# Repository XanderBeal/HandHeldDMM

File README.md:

Does this work as a text file???

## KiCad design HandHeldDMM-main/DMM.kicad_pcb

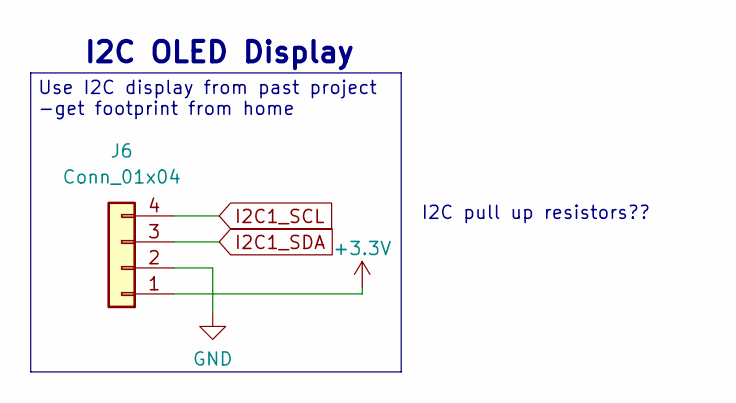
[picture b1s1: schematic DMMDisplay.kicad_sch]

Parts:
J6: Conn_01x04; PinHeader_1x04_P2.54mm_Vertical; LCSC Price 0

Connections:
GND: J6.2; also elsewhere on the board
I2C1_SCL: J6.4; also elsewhere on the board
I2C1_SDA: J6.3; also elsewhere on the board

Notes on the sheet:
Use I2C display from past project -get footprint from home
I2C pull up resistors??
I2C OLED Display

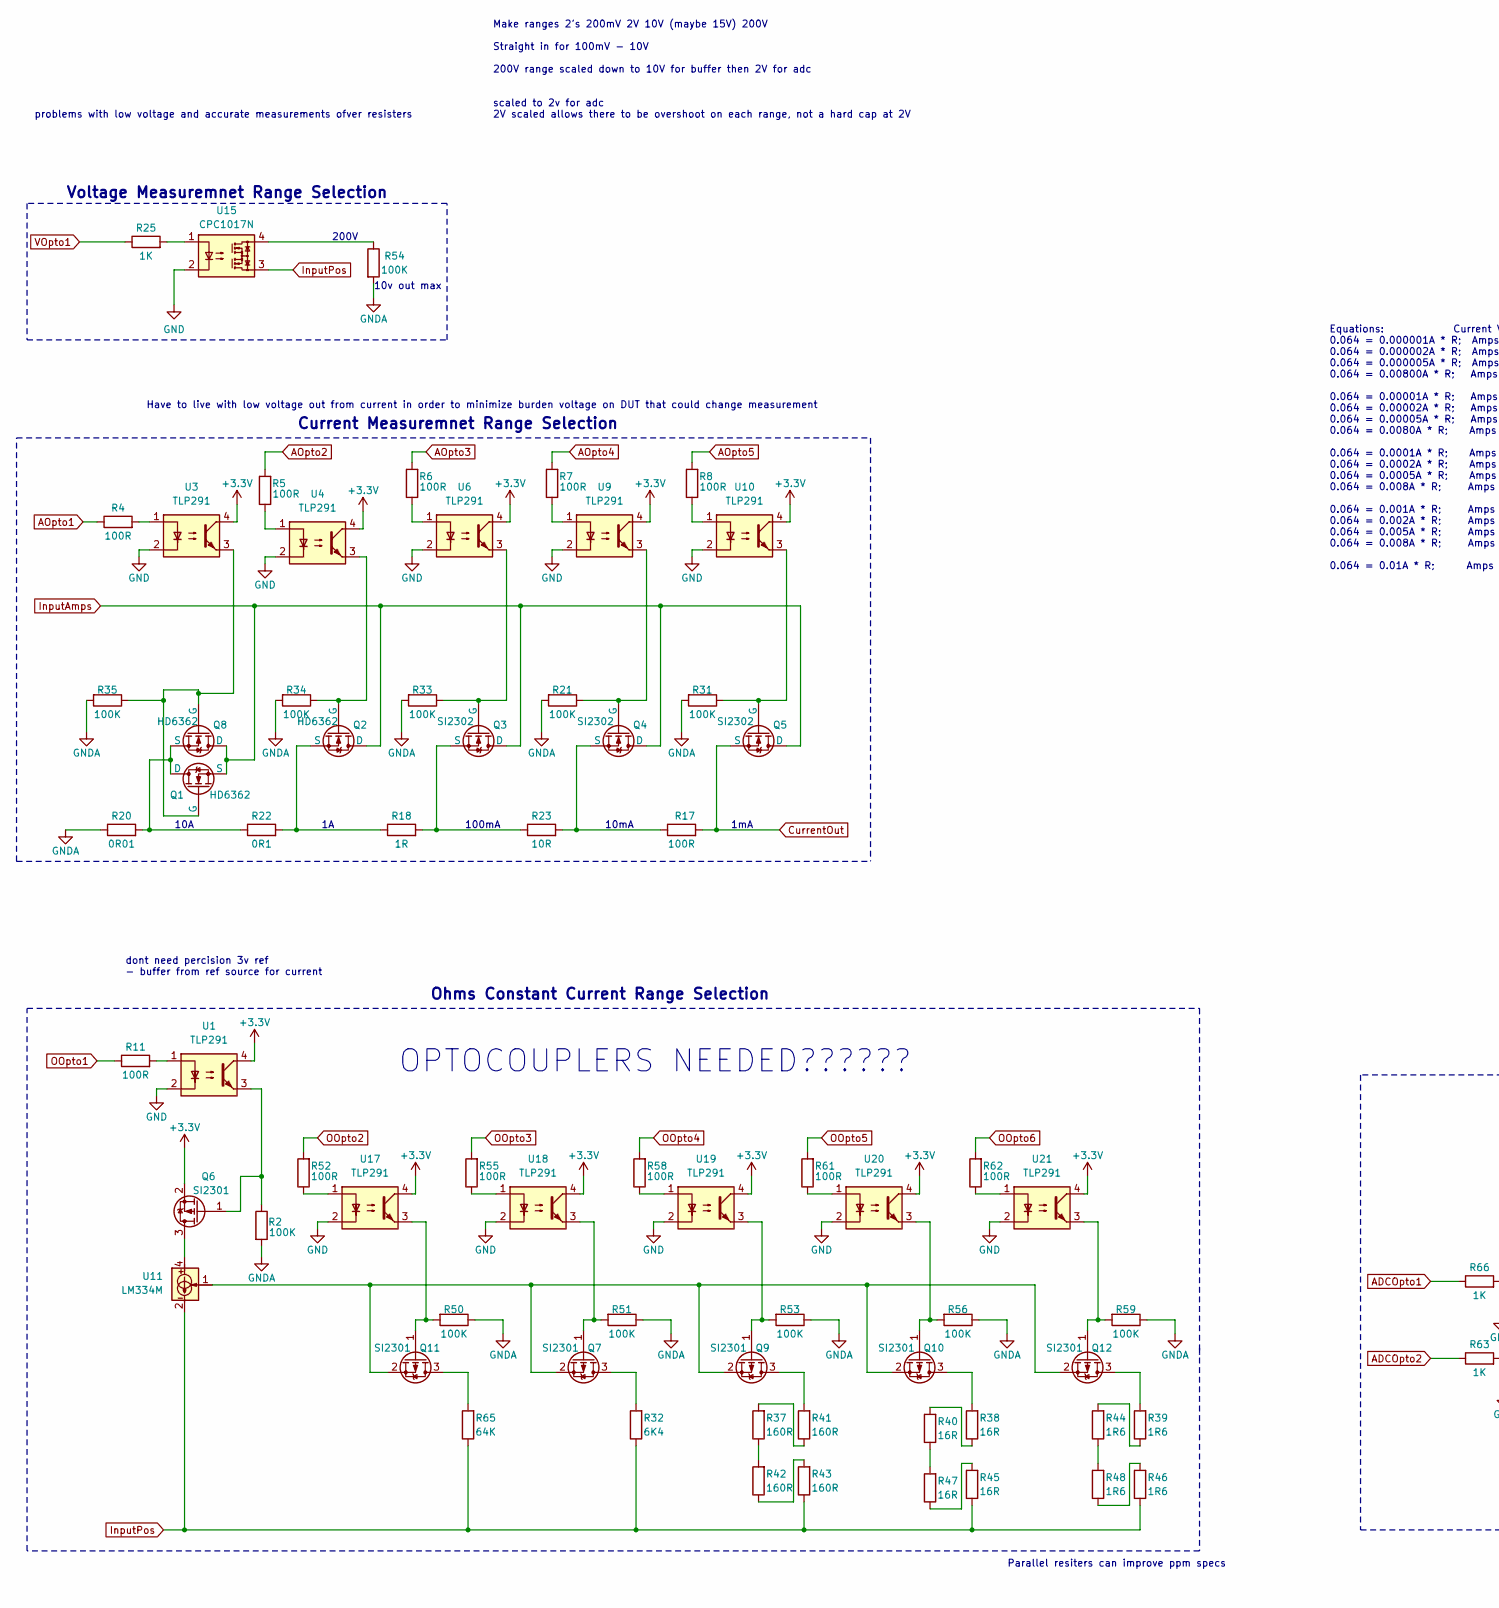
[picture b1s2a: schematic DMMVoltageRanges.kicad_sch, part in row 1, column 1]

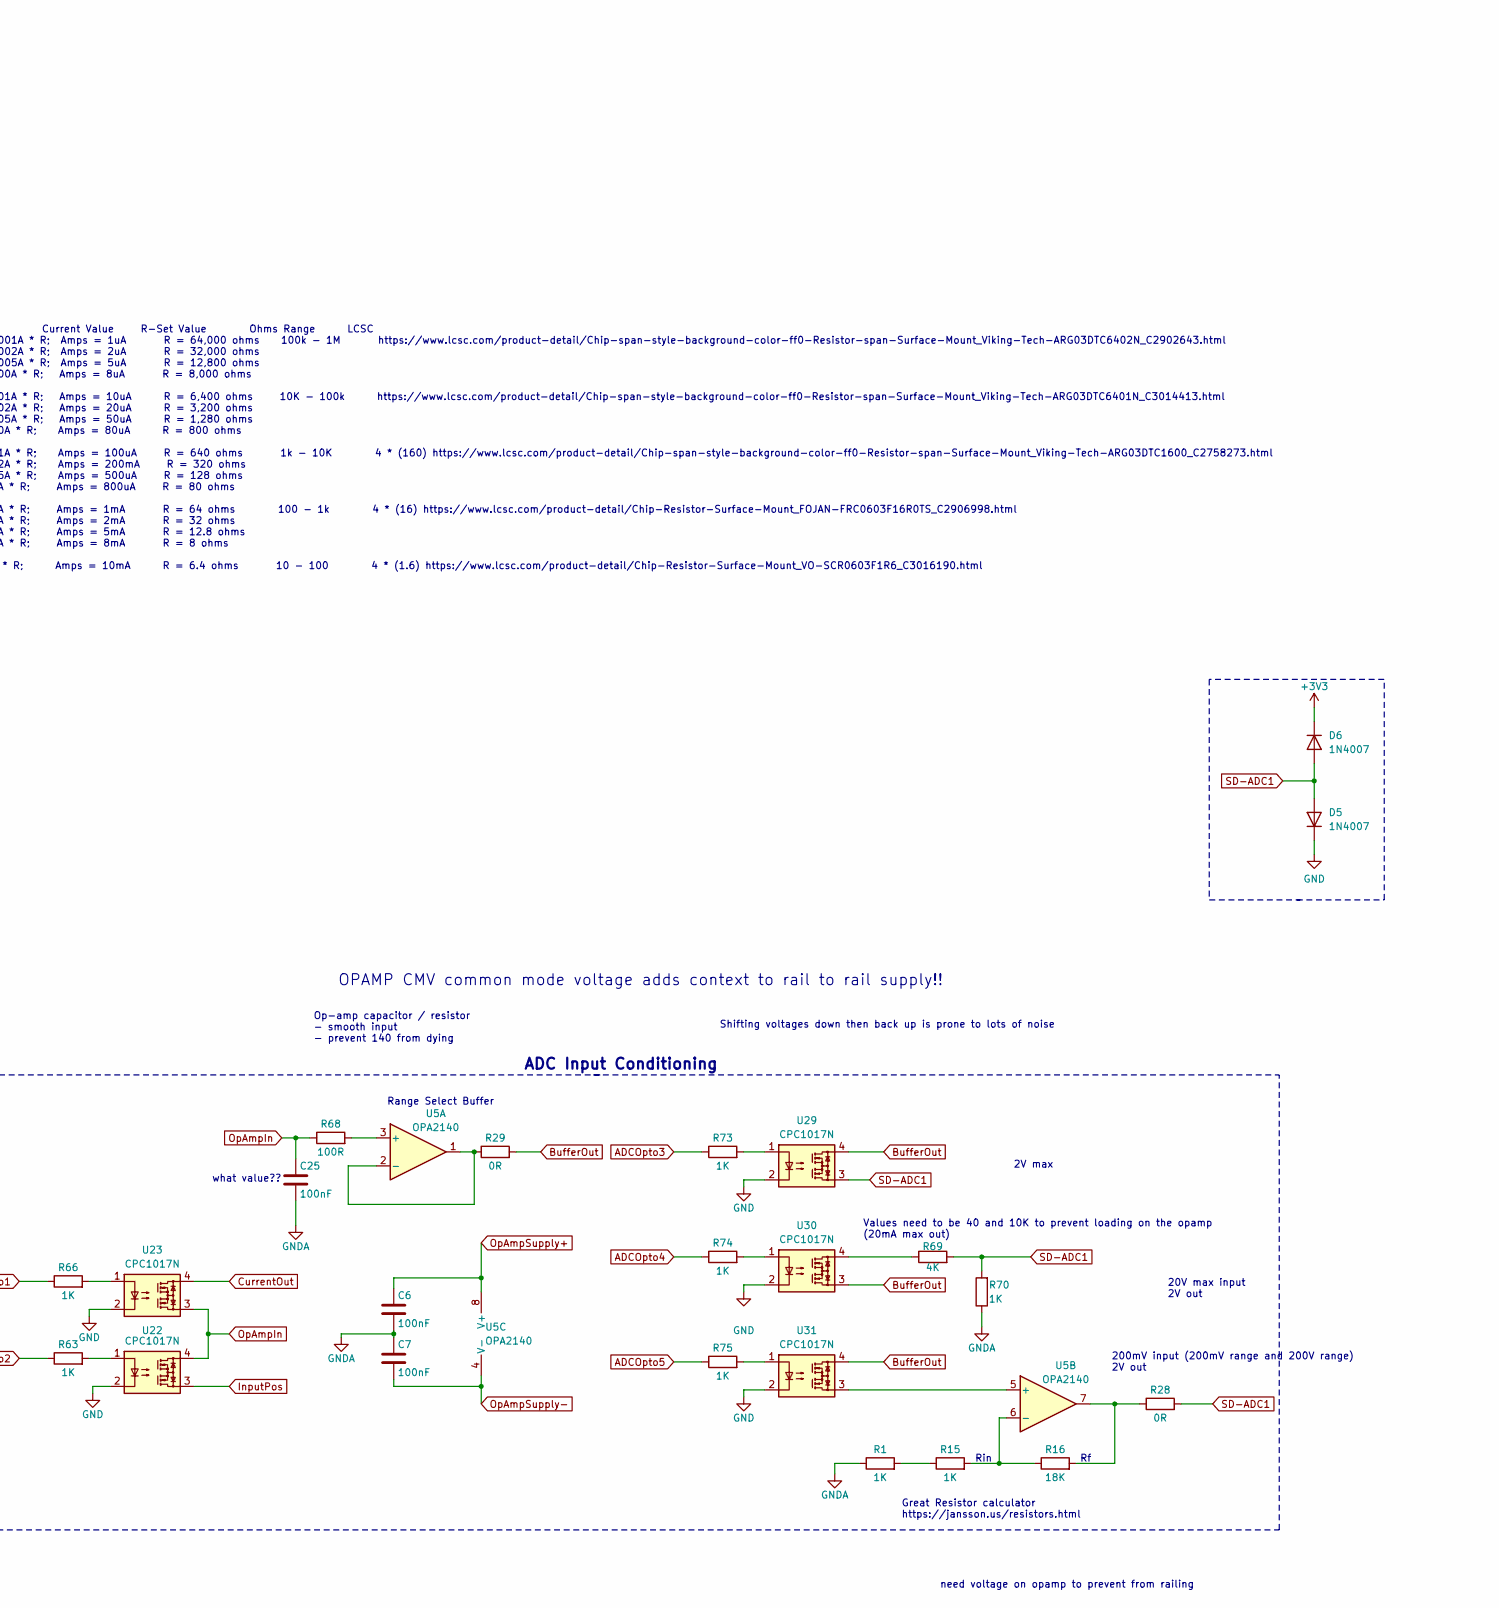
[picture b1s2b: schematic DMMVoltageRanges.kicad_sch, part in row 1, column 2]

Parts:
C6, C7, C25: 100nF; C_0402_1005Metric_Pad0.74x0.62mm_HandSolder; PART# C513772; LCSC Price 0.18
D5, D6: 1N4007; D_DO-41_SOD81_P10.16mm_Horizontal
Q1, Q2, Q8: HD6362; TO-252-2; PART# C5451644; LCSC Price 2
Q3, Q4, Q5: SI2302; SOT-23; PART# C4748714; LCSC Price 0.58
Q6, Q7, Q9, Q10, Q11, Q12: SI2301; SOT-23; PART# C5261052; LCSC Price 0.59
R1, R15, R25, R63, R66, R70, R73, R74, R75: 1K; R_0603_1608Metric_Pad0.98x0.95mm_HandSolder; PART# C5141145; LCSC Price 0.25
R2, R21, R31, R33, R34, R35, R50, R51, R53, R54, R56, R59: 100K; R_0603_1608Metric_Pad0.98x0.95mm_HandSolder; PART# C2906980; LCSC Price 0.09
R4, R5, R6, R7, R8, R11, R52, R55, R58, R61, R62, R68: 100R; R_0402_1005Metric_Pad0.72x0.64mm_HandSolder; PART# C2906860; LCSC Price 0.05
R16: 18K; R_0402_1005Metric_Pad0.72x0.64mm_HandSolder; PART# C2984412; LCSC Price 0.45
R17: 100R; R_2512_6332Metric_Pad1.40x3.35mm_HandSolder; PART# C105063; LCSC Price 0.3
R18: 1R; R_2512_6332Metric_Pad1.40x3.35mm_HandSolder; PART# C5127856; LCSC Price 0.89
R20: 0R01; Shunt L10mm PAD1mm; PART# C487937; LCSC Price 1.62
R22: 0R1; R_2512_6332Metric_Pad1.40x3.35mm_HandSolder; PART# C841792; LCSC Price 0.38
R23: 10R; R_2512_6332Metric_Pad1.40x3.35mm_HandSolder; PART# C105071; LCSC Price 0.48
R28, R29: 0R; R_0603_1608Metric_Pad0.98x0.95mm_HandSolder; PART# C2907080; LCSC Price 0.09
R32: 6K4; R_0402_1005Metric_Pad0.72x0.64mm_HandSolder; PART# C3014413; LCSC Price 0.42
R37, R41, R42, R43: 160R; R_0402_1005Metric_Pad0.72x0.64mm_HandSolder; PART# C2933075; LCSC Price 0.05
R38, R40, R45, R47: 16R; R_0402_1005Metric_Pad0.72x0.64mm_HandSolder; PART# C3015729; LCSC Price 0.05
R39, R44, R46, R48: 1R6; R_0402_1005Metric_Pad0.72x0.64mm_HandSolder; PART# C3015705; LCSC Price 0.07
R65: 64K; R_1206_3216Metric_Pad1.30x1.75mm_HandSolder; PART# C3037190; LCSC Price 0.19
R69: 4K; R_0603_1608Metric_Pad0.98x0.95mm_HandSolder; PART# C2984443; LCSC Price 0.42
U1, U3, U4, U6, U9, U10, U17, U18, U19, U20, U21: TLP291; SOP-4_4.4x2.6mm_P1.27mm; PART# C3018819; LCSC Price 1.32
U5: OPA2140; SOP-8_3.9x4.9mm_P1.27mm; PART# C335586; LCSC Price 15.31
U11: LM334M; SOIC-8_3.9x4.9mm_P1.27mm; PART# C7945; LCSC Price 2.63
U15, U22, U23, U29, U30, U31: CPC1017N; SOP-4_3.8x4.1mm_P2.54mm; PART# C81521; LCSC Price 0.67

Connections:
ADCOpto1: R66.1; also elsewhere on the board
ADCOpto2: R63.1; also elsewhere on the board
ADCOpto3: R73.1; also elsewhere on the board
ADCOpto4: R74.1; also elsewhere on the board
ADCOpto5: R75.1; also elsewhere on the board
AOpto1: R4.1; also elsewhere on the board
AOpto2: R5.2; also elsewhere on the board
AOpto3: R6.2; also elsewhere on the board
AOpto4: R7.2; also elsewhere on the board
AOpto5: R8.2; also elsewhere on the board
BufferOut: R29.2, U29.4, U30.3, U31.4
CurrentOut: Q5.3 (S), R17.2, U23.4
GND: C6.2, C7.1, C25.2, D5.1 (K), R1.1, R2.2, R20.1, R21.2, R31.2, R33.2, R34.2, R35.2, R50.1, R51.1, R53.1, R54.2, R56.1, R59.1, R70.1, U1.2, U3.2, U4.2, U6.2, U9.2, U10.2, U15.2, U17.2, U18.2, U19.2, U20.2, U21.2, U22.2, U23.2, U29.2, U30.2, U31.2; also elsewhere on the board
InputAmps: Q1.3 (S), Q2.2 (D), Q3.2 (D), Q4.2 (D), Q5.2 (D), Q8.2 (D); also elsewhere on the board
InputPos: R32.1, R43.1, R45.1, R46.1, R65.1, U11.2, U11.3, U11.6, U11.7, U15.3, U22.3; also elsewhere on the board
unnamed: Q1.2 (D), Q8.3 (S), R20.2, R22.1
unnamed: Q1.1 (G), Q8.1 (G), R35.1, U3.3
unnamed: Q2.1 (G), R34.1, U4.3
unnamed: Q2.3 (S), R18.1, R22.2
unnamed: Q3.1 (G), R33.1, U6.3
unnamed: Q3.3 (S), R18.2, R23.1
unnamed: Q4.1 (G), R21.1, U9.3
unnamed: Q4.3 (S), R17.1, R23.2
unnamed: Q5.1 (G), R31.1, U10.3
unnamed: Q6.3 (D), U11.4
unnamed: Q6.1 (G), R2.1, U1.3
unnamed: Q7.3 (D), R32.2
unnamed: Q7.1 (G), R51.2, U18.3
unnamed: Q9.3 (D), R41.2
unnamed: Q9.1 (G), R53.2, U19.3
unnamed: Q10.3 (D), R38.2
unnamed: Q10.1 (G), R56.2, U20.3
unnamed: Q7.2 (S), Q9.2 (S), Q10.2 (S), Q11.2 (S), Q12.2 (S), U11.1
unnamed: Q11.3 (D), R65.2
unnamed: Q11.1 (G), R50.2, U17.3
unnamed: Q12.3 (D), R39.2
unnamed: Q12.1 (G), R59.2, U21.3
unnamed: R1.2, R15.1
unnamed: R4.2, U3.1
unnamed: R5.1, U4.1
unnamed: R6.1, U6.1
unnamed: R7.1, U9.1
unnamed: R8.1, U10.1
unnamed: R11.2, U1.1
unnamed: R16.2, R28.1, U5.7
unnamed: R25.2, U15.1
unnamed: R37.1, R42.2
unnamed: R37.2, R41.1
unnamed: R38.1, R40.2
unnamed: R39.1, R44.2
unnamed: R40.1, R47.2
unnamed: R42.1, R43.2
unnamed: R44.1, R48.2
unnamed: R45.2, R47.1
unnamed: R46.2, R48.1
unnamed: R52.1, U17.1
unnamed: R54.1, U15.4
unnamed: R55.1, U18.1
unnamed: R58.1, U19.1
unnamed: R61.1, U20.1
unnamed: R62.1, U21.1
unnamed: R63.2, U22.1
unnamed: R66.2, U23.1
unnamed: R69.1, U30.4
unnamed: R73.2, U29.1
unnamed: R74.2, U30.1
unnamed: R75.2, U31.1
unnamed: R68.2, U5.3 (+)
unnamed: R29.1, U5.1, U5.2 (-)
unnamed: U5.5 (+), U31.3
unnamed: R15.2, R16.1, U5.6 (-)
OOpto1: R11.1; also elsewhere on the board
OOpto2: R52.2; also elsewhere on the board
OOpto3: R55.2; also elsewhere on the board
OOpto4: R58.2; also elsewhere on the board
OOpto5: R61.2; also elsewhere on the board
OOpto6: R62.2; also elsewhere on the board
OpAmpIn: C25.1, R68.1, U22.4, U23.3
OpAmpSupply+: C6.1, U5.8 (V+); also elsewhere on the board
OpAmpSupply-: C7.2, U5.4 (V-); also elsewhere on the board
SD-ADC1: D5.2 (A), D6.2 (A), R28.2, R69.2, R70.2, U29.3; also elsewhere on the board
VOpto1: R25.1; also elsewhere on the board

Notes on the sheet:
Range Select Buffer
Voltage Measuremnet Range Selection
2V max
need voltage on opamp to prevent from railing
10v out max
Op-amp capacitor / resistor - smooth input - prevent 140 from dying
10mA
Values need to be 40 and 10K to prevent loading on the opamp (20mA max out)
1mA
Have to live with low voltage out from current in order to minimize burden voltage on DUT that could change measurement
Current Measuremnet Range Selection
Great Resistor calculator https://jansson.us/resistors.html
Shifting voltages down then back up is prone to lots of noise
Parallel resiters can improve ppm specs
dont need percision 3v ref - buffer from ref source for current
ADC Input Conditioning
Ohms Constant Current Range Selection
Rin
OPTOCOUPLERS NEEDED??????
Equations: Current Value R-Set Value Ohms Range LCSC 0.064 = 0.000001A * R; Amps = 1uA R = 64,000 ohms 100k - 1M https://www.lcsc.com/product-detail/Chip-span-style-background-color-ff0-Resistor-span-Surface-Mount_Viking-Tech-ARG03DTC6402N_C2902643.html 0.064 = 0.000002A * R; Amps = 2uA R = 32,000 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
10A
200mV input (200mV range and 200V range) 2V out
Make ranges 2's 200mV 2V 10V (maybe 15V) 200V Straight in for 100mV - 10V 200V range scaled down to 10V for buffer then 2V for adc scaled to 2v for adc 2V scaled allows there to be overshoot on each range, not a hard cap at 2V
OPAMP CMV common mode voltage adds context to rail to rail supply!!
200V
100mA
what value??
20V max input 2V out
problems with low voltage and accurate measurements ofver resisters

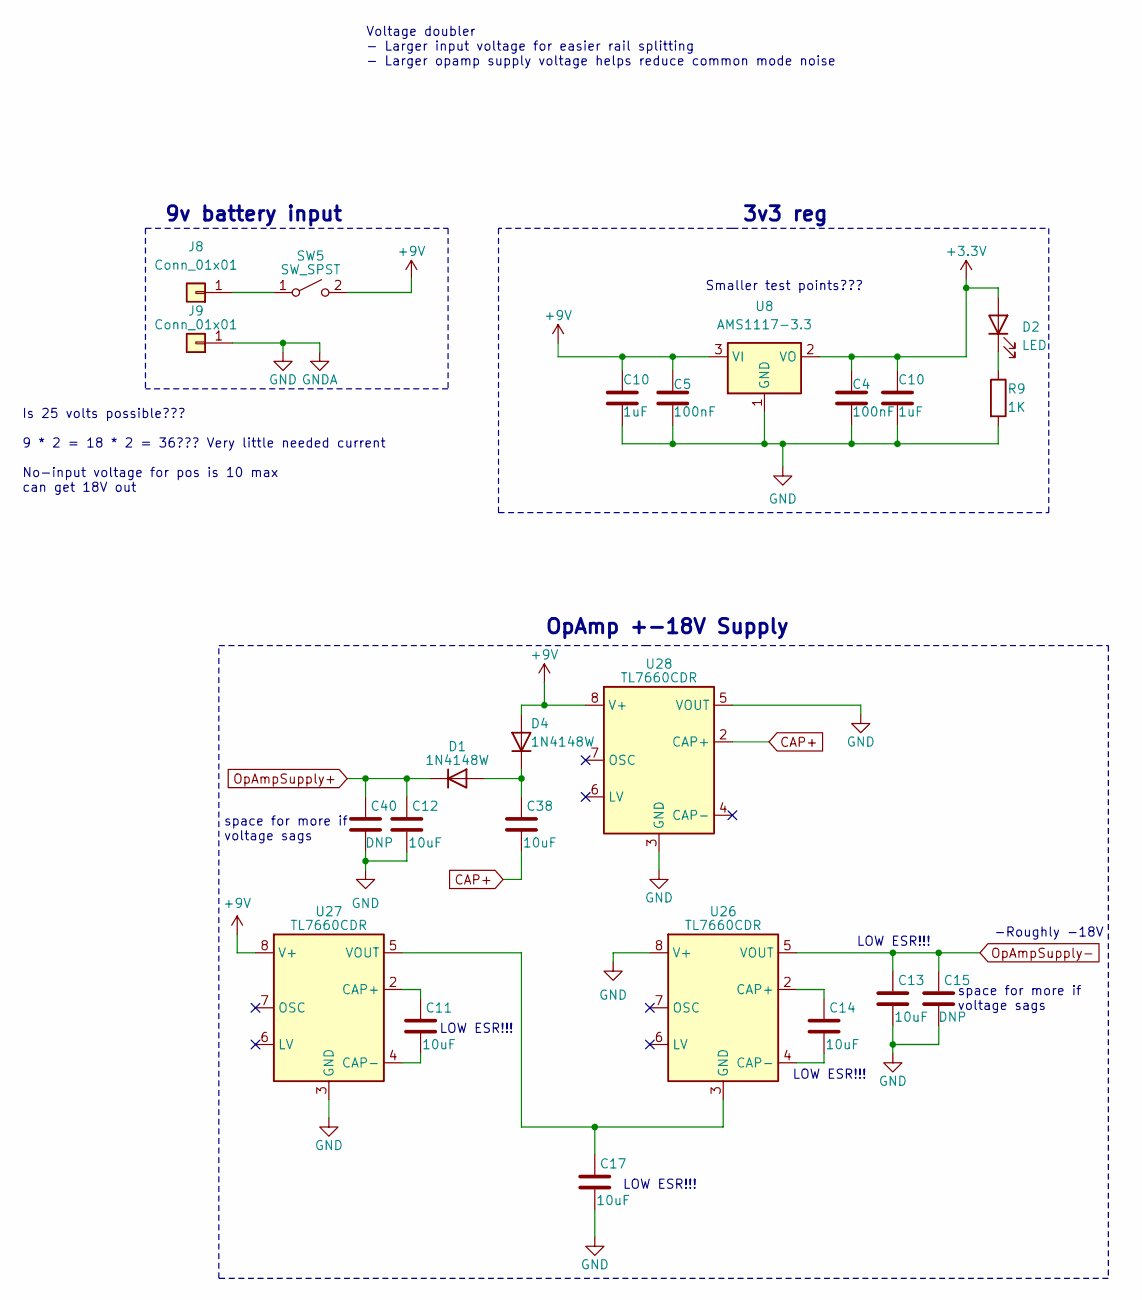
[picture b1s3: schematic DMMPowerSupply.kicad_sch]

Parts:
C4, C5: 100nF; C_0402_1005Metric_Pad0.74x0.62mm_HandSolder; PART# C513772; LCSC Price 0.18
C10: 1uF; C_0402_1005Metric_Pad0.74x0.62mm_HandSolder; PART# C14445; LCSC Price 0.17
C11, C12, C13, C14, C17, C38: 10uF; C_1206_3216Metric_Pad1.33x1.80mm_HandSolder; PART# C5189826; LCSC Price 0.41
C15, C40: DNP; C_1206_3216Metric_Pad1.33x1.80mm_HandSolder
D1, D4: 1N4148W; D_SOD-123; PART# C917030; LCSC Price 0.52
D2: LED; LED_0603_1608Metric_Pad1.05x0.95mm_HandSolder; LCSC Price 0
J8, J9: Conn_01x01; TestPoint_THTPad_3.0x3.0mm_Drill1.5mm; LCSC Price 0
R9: 1K; R_0603_1608Metric_Pad0.98x0.95mm_HandSolder; PART# C5141145; LCSC Price 0.25
SW5: SW_SPST; Dip Switch
U8: AMS1117-3.3; SOT-89-3; PART# C5345982; LCSC Price 0.39
U26, U27, U28: TL7660CDR; SOIC-8_3.9x4.9mm_P1.27mm; PART# C130206

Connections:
CAP+: C38.1, U28.2 (CAP+)
GND: C4.2, C5.2, C10.2, C12.1, C13.1, C15.1, C17.1, C40.1, J9.1, R9.2, U8.1 (GND), U26.8 (V+), U27.3 (GND), U28.3 (GND), U28.5 (VOUT); also elsewhere on the board
unnamed: C38.2, D1.2 (A), D4.1 (K)
unnamed: D2.1 (K), R9.1
unnamed: J8.1, SW5.1 (A)
unnamed: C14.2, U26.2 (CAP+)
unnamed: C14.1, U26.4 (CAP-)
unnamed: C17.2, U26.3 (GND), U27.5 (VOUT)
unnamed: C11.2, U27.2 (CAP+)
unnamed: C11.1, U27.4 (CAP-)
OpAmpSupply+: C12.2, C40.2, D1.1 (K); also elsewhere on the board
OpAmpSupply-: C13.2, C15.2, U26.5 (VOUT); also elsewhere on the board

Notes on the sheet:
-Roughly -18V
LOW ESR!!!
3v3 reg
Is 25 volts possible??? 9 * 2 = 18 * 2 = 36??? Very little needed current No-input voltage for pos is 10 max can get 18V out
OpAmp +-18V Supply
Smaller test points???
Voltage doubler - Larger input voltage for easier rail splitting - Larger opamp supply voltage helps reduce common mode noise
9v battery input
space for more if voltage sags

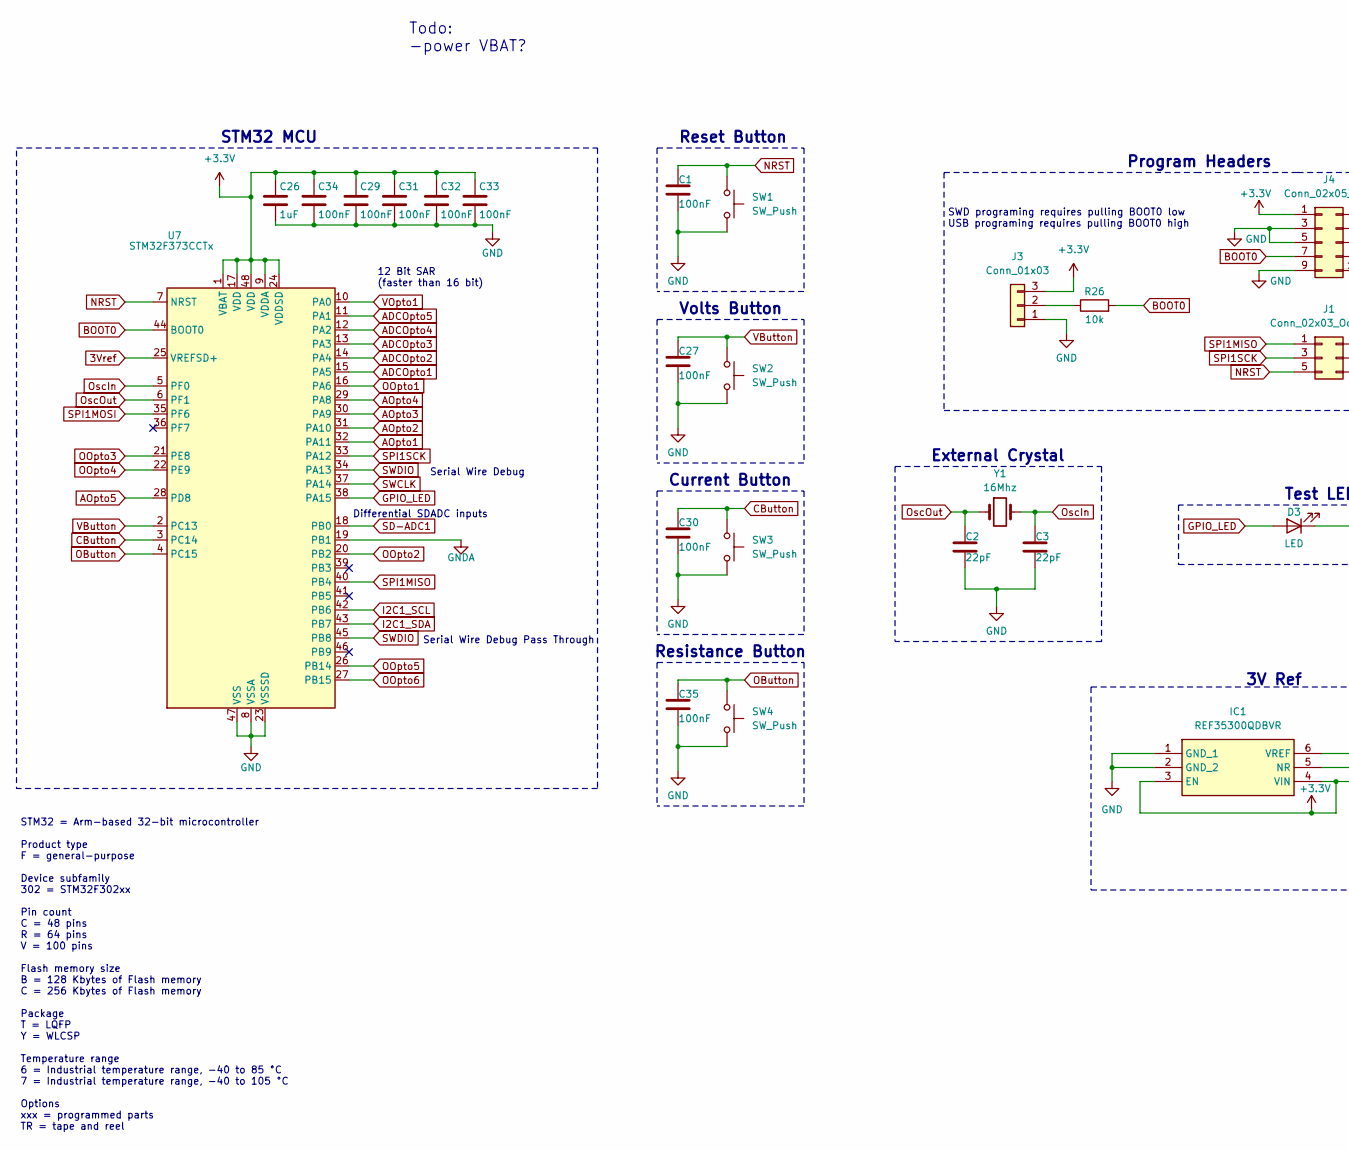
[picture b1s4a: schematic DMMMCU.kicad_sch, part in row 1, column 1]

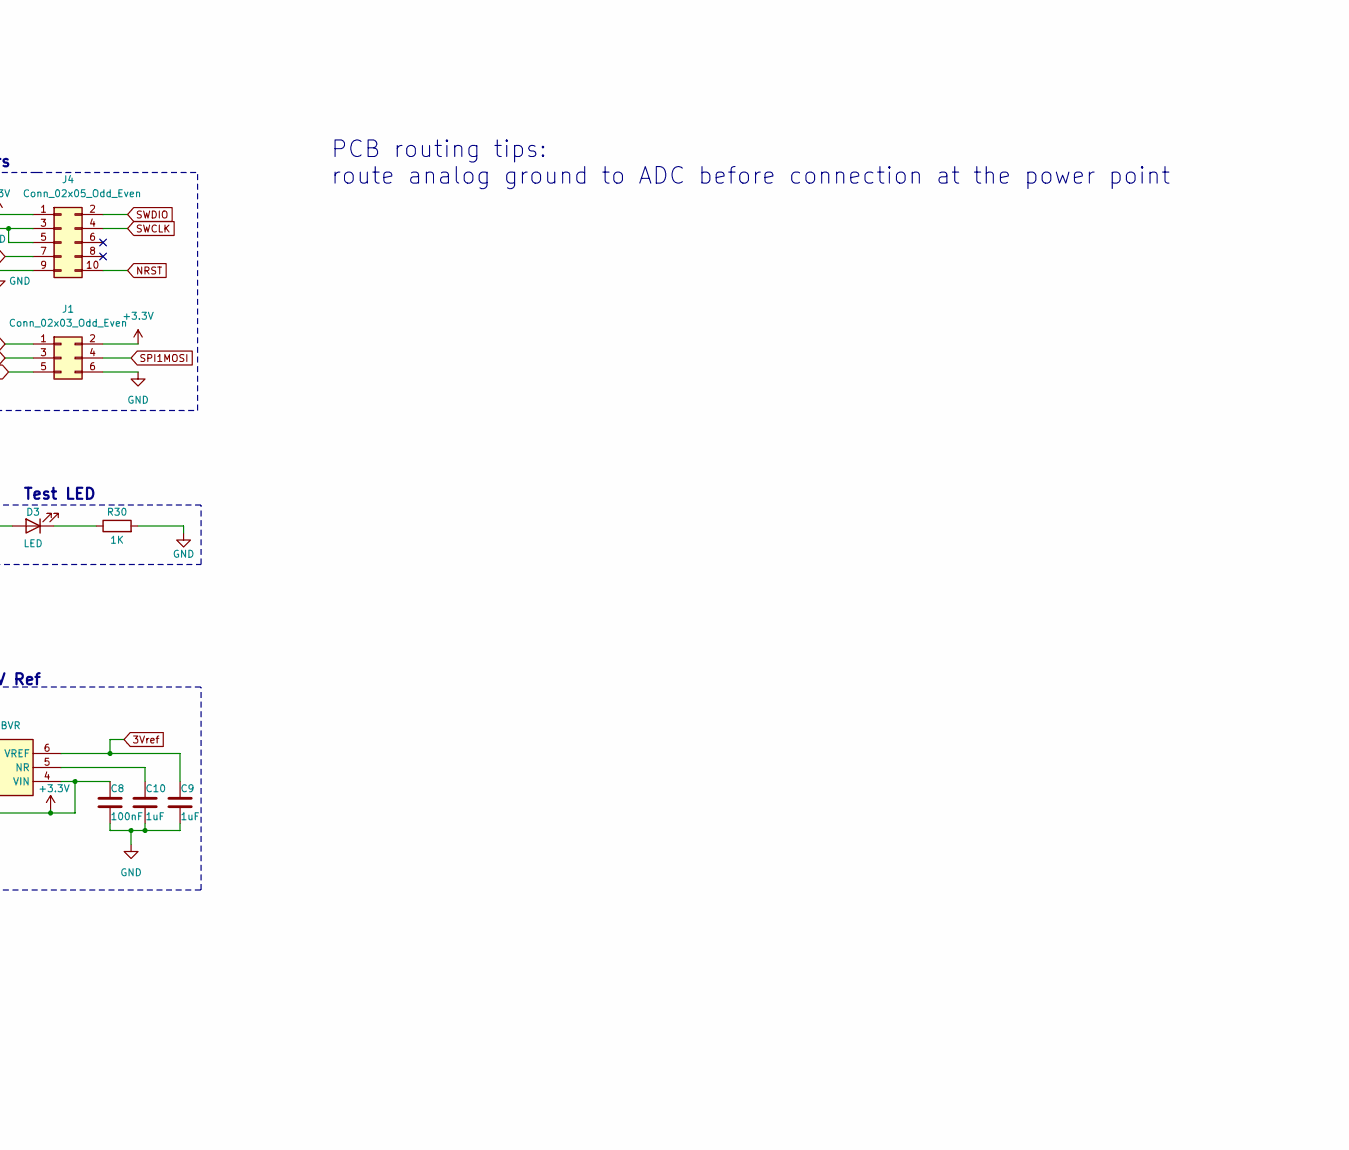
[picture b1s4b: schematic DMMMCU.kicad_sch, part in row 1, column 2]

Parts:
C1, C8, C27, C29, C30, C31, C32, C33, C34, C35: 100nF; C_0402_1005Metric_Pad0.74x0.62mm_HandSolder; PART# C513772; LCSC Price 0.18
C2, C3: 22pF; C_0402_1005Metric_Pad0.74x0.62mm_HandSolder; LCSC Price 0
C9, C10, C26: 1uF; C_0402_1005Metric_Pad0.74x0.62mm_HandSolder; PART# C14445; LCSC Price 0.17
D3: LED; LED_0603_1608Metric_Pad1.05x0.95mm_HandSolder; LCSC Price 0
IC1: REF35300QDBVR; SOT-23-6; PART# C6643299; LCSC Price 3.09
J1: Conn_02x03_Odd_Even; PinHeader_2x03_P2.54mm_Vertical; LCSC Price 0
J3: Conn_01x03; PinHeader_1x03_P2.54mm_Vertical; LCSC Price 0
J4: Conn_02x05_Odd_Even; PinHeader_2x05_P2.54mm_Vertical; LCSC Price 0
R26: 10k; R_0603_1608Metric_Pad0.98x0.95mm_HandSolder; PART# C103199; LCSC Price copy
R30: 1K; R_0603_1608Metric_Pad0.98x0.95mm_HandSolder; PART# C5141145; LCSC Price 0.25
SW1, SW2, SW3, SW4: SW_Push; SW_SPST_B3S-1000; PART# C2888900; LCSC Price 0.4
U7: STM32F373CCTx; LQFP-48_7x7mm_P0.5mm; PART# C89403; LCSC Price 20.27
Y1: 16Mhz; Crystal_DS10_D1.0mm_L4.3mm_Vertical; LCSC Price 0

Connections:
3Vref: C9.1, IC1.6 (VREF), U7.25 (VREFSD+)
ADCOpto1: U7.15 (PA5); also elsewhere on the board
ADCOpto2: U7.14 (PA4); also elsewhere on the board
ADCOpto3: U7.13 (PA3); also elsewhere on the board
ADCOpto4: U7.12 (PA2); also elsewhere on the board
ADCOpto5: U7.11 (PA1); also elsewhere on the board
AOpto1: U7.32 (PA11); also elsewhere on the board
AOpto2: U7.31 (PA10); also elsewhere on the board
AOpto3: U7.30 (PA9); also elsewhere on the board
AOpto4: U7.29 (PA8); also elsewhere on the board
AOpto5: U7.28 (PD8); also elsewhere on the board
BOOT0: J4.7, R26.2, U7.44 (BOOT0)
CButton: C30.1, SW3.1, U7.3 (PC14)
GND: C1.2, C2.2, C3.2, C8.2, C9.2, C10.2, C26.2, C27.2, C29.2, C30.2, C31.2, C32.2, C33.2, C34.2, C35.2, IC1.1 (GND_1), IC1.2 (GND_2), J1.6, J3.1, J4.3, J4.5, J4.9, R30.2, SW1.2, SW2.2, SW3.2, SW4.2, U7.8 (VSSA), U7.19 (PB1), U7.23 (VSSSD), U7.47 (VSS); also elsewhere on the board
GPIO_LED: D3.2 (A), U7.38 (PA15)
I2C1_SCL: U7.42 (PB6); also elsewhere on the board
I2C1_SDA: U7.43 (PB7); also elsewhere on the board
NRST: C1.1, J1.5, J4.10, SW1.1, U7.7 (NRST)
unnamed: D3.1 (K), R30.1
unnamed: J3.2, R26.1
OButton: C35.1, SW4.1, U7.4 (PC15)
OOpto1: U7.16 (PA6); also elsewhere on the board
OOpto2: U7.20 (PB2); also elsewhere on the board
OOpto3: U7.21 (PE8); also elsewhere on the board
OOpto4: U7.22 (PE9); also elsewhere on the board
OOpto5: U7.26 (PB14); also elsewhere on the board
OOpto6: U7.27 (PB15); also elsewhere on the board
OscIn: C3.1, U7.5 (PF0), Y1.2
OscOut: C2.1, U7.6 (PF1), Y1.1
SD-ADC1: U7.18 (PB0); also elsewhere on the board
SPI1MISO: J1.1, U7.40 (PB4)
SPI1MOSI: J1.4, U7.35 (PF6)
SPI1SCK: J1.3, U7.33 (PA12)
SWCLK: J4.4, U7.37 (PA14)
SWDIO: J4.2, U7.34 (PA13), U7.45 (PB8)
VButton: C27.1, SW2.1, U7.2 (PC13)
VOpto1: U7.10 (PA0); also elsewhere on the board

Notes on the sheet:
External Crystal
Volts Button
STM32 MCU
SWD programing requires pulling BOOT0 low USB programing requires pulling BOOT0 high
Resistance Button
3V Ref
Reset Button
Current Button
Test LED
Todo: -power VBAT?
Program Headers
PCB routing tips: route analog ground to ADC before connection at the power point
Serial Wire Debug
Serial Wire Debug Pass Through
Differential SDADC inputs
12 Bit SAR (faster than 16 bit)
STM32 = Arm-based 32-bit microcontroller Product type F = general-purpose Device subfamily 302 = STM32F302xx Pin count C = 48 pins R = 64 pins V = 100 pins Flash memory size B = 128 Kbytes of Flash memory C = 256 Kbytes of Flash memory Package T = LQFP Y = WLCSP Temperature range 6 = Industrial tem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

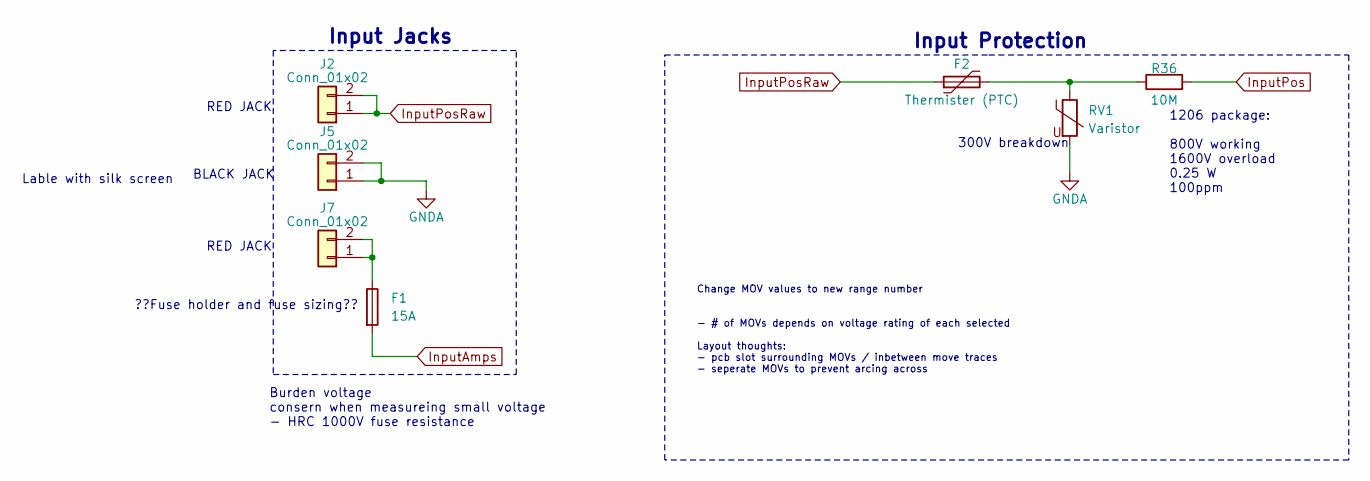
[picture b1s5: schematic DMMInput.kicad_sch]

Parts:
F1: 15A; Fuse holder; PART# C3130; LCSC Price 0.35
F2: Thermister (PTC); R_Axial_DIN0207_L6.3mm_D2.5mm_P7.62mm_Horizontal; LCSC Price 0
J2, J7: Conn_01x02; Bannana Input Jack; PART# C7437321; LCSC Price 0.9180
J5: Conn_01x02; Bannana Input Jack; PART# C7437322; LCSC Price 0.9180
R36: 10M; R_1206_3216Metric_Pad1.30x1.75mm_HandSolder; PART# C2078785; LCSC Price 1.19
RV1: Varistor; R_Axial_DIN0207_L6.3mm_D2.5mm_P5.08mm_Vertical; PART# C283925; LCSC Price 0.6

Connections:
GND: J5.1, J5.2, RV1.2; also elsewhere on the board
InputAmps: F1.2; also elsewhere on the board
InputPos: R36.2; also elsewhere on the board
InputPosRaw: F2.1, J2.1, J2.2
unnamed: F2.2, R36.1, RV1.1
unnamed: F1.1, J7.1, J7.2

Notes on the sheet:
RED JACK
1206 package: 800V working 1600V overload 0.25 W 100ppm
300V breakdown
Burden voltage consern when measureing small voltage - HRC 1000V fuse resistance
Lable with silk screen
Input Jacks
??Fuse holder and fuse sizing??
Change MOV values to new range number - # of MOVs depends on voltage rating of each selected Layout thoughts: - pcb slot surrounding MOVs / inbetween move traces - seperate MOVs to prevent arcing across
BLACK JACK
Input Protection

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
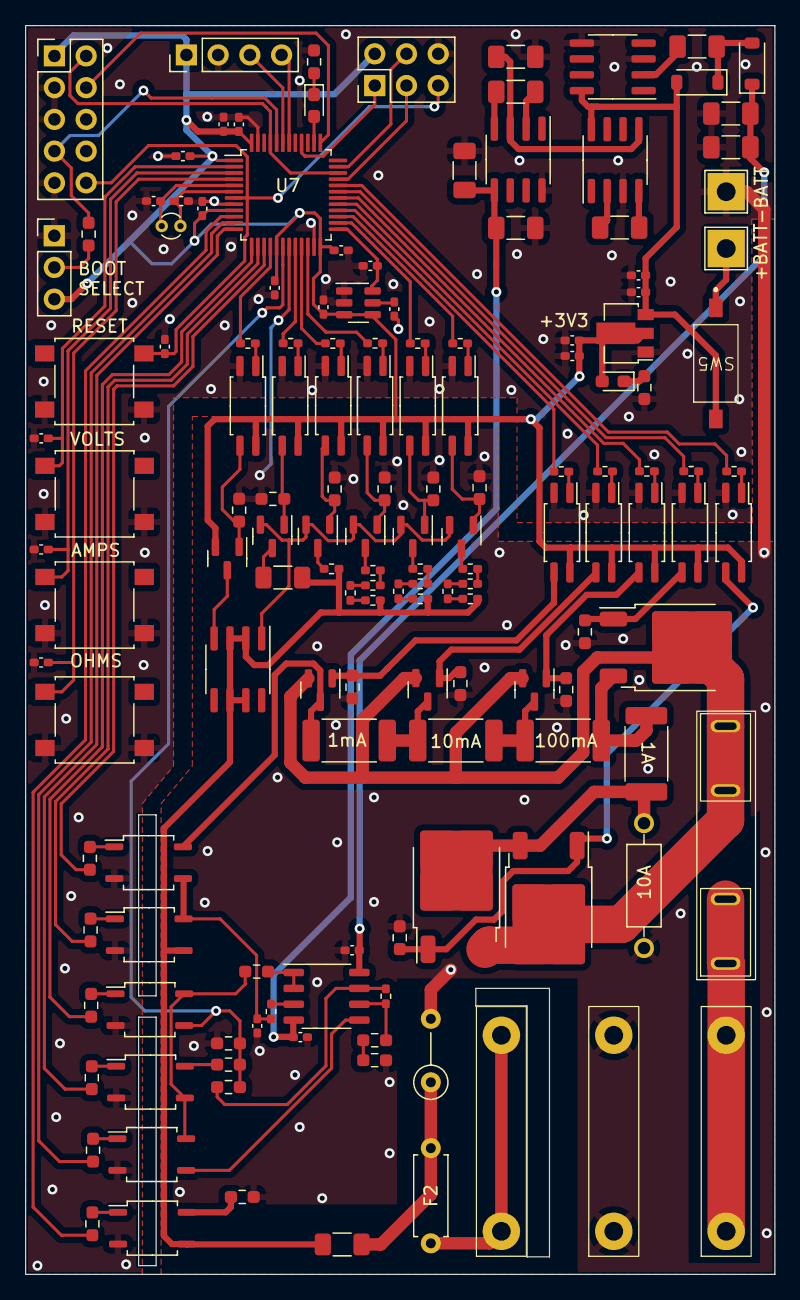
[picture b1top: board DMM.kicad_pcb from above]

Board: 2 copper layers, 60.0 x 100.0 mm, 149 parts (0 on the bottom side), 115 nets.

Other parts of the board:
C16, C18: 1uF; C_0402_1005Metric_Pad0.74x0.62mm_HandSolder

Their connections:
GND: C16.2, C18.2; also elsewhere on the board

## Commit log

2023-10-20 DMM Files first upload
2023-11-15 Trial Layout and routing
2023-11-15 deleated files
2023-11-15 PCB work
2023-11-16 More pcb work
2023-11-16 PCB rev 1 with schematic change ideas
2023-11-19 Its going
2023-11-20 Layout / routing V2 with schematic fixes
2023-11-20 Finished?
2023-11-20 Finished
2023-11-20 Ordered
2023-12-05 schematic fixes
2023-12-07 fixes for v2
2023-12-08 clear
2023-12-08 First add
2023-12-08 First fix?
2023-12-08 does this Verk?
2023-12-08 still verks??
2023-12-08 NOT BIPOLAR ADC YOU DUMBASS!!!!
2023-12-08 veerks???????
2023-12-08 schematic changes
2023-12-08 Pull from rev1
2023-12-08 final changes before rev 2 creation
2023-12-08 misc
2023-12-08 remove kicad files
2023-12-08 test
2023-12-08 test2
2023-12-08 save
2023-12-09 working
2023-12-10 screen wont work???
2023-12-10 one step forword, one step back
2023-12-10 UI being hard to work with
2023-12-11 IT REALLY VERKS!
2023-12-11 AMPS test
2023-12-11 Dumb Fix to ranging
2023-12-11 linear gain error fix??
2023-12-12 wrong cal
2023-12-14 message
2023-12-14 messing around with adc
2023-12-14 just saving
2023-12-14 why is current not changing ranges???
2023-12-15 work on amps
2023-12-15 LatestDMM_No amps_Or_ohms
